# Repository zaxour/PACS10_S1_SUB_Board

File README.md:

# PACS10_S1_SUB_Board

This schematic is, to the best of my ability, a complete capture of the SSUB board found on the PAC-S10 and S1. It is based on the later revision which incorporates the KOSUB board (aka the "bodge board") into the regular layout, as well as the updates made to the audio circuit, which are detailed in a service bulletin. I have included the EAGLE design files (.brd/.sch) as well for anyone that wants to take a crack at laying out the board and producing a new one, if I don't end up doing it at some point.

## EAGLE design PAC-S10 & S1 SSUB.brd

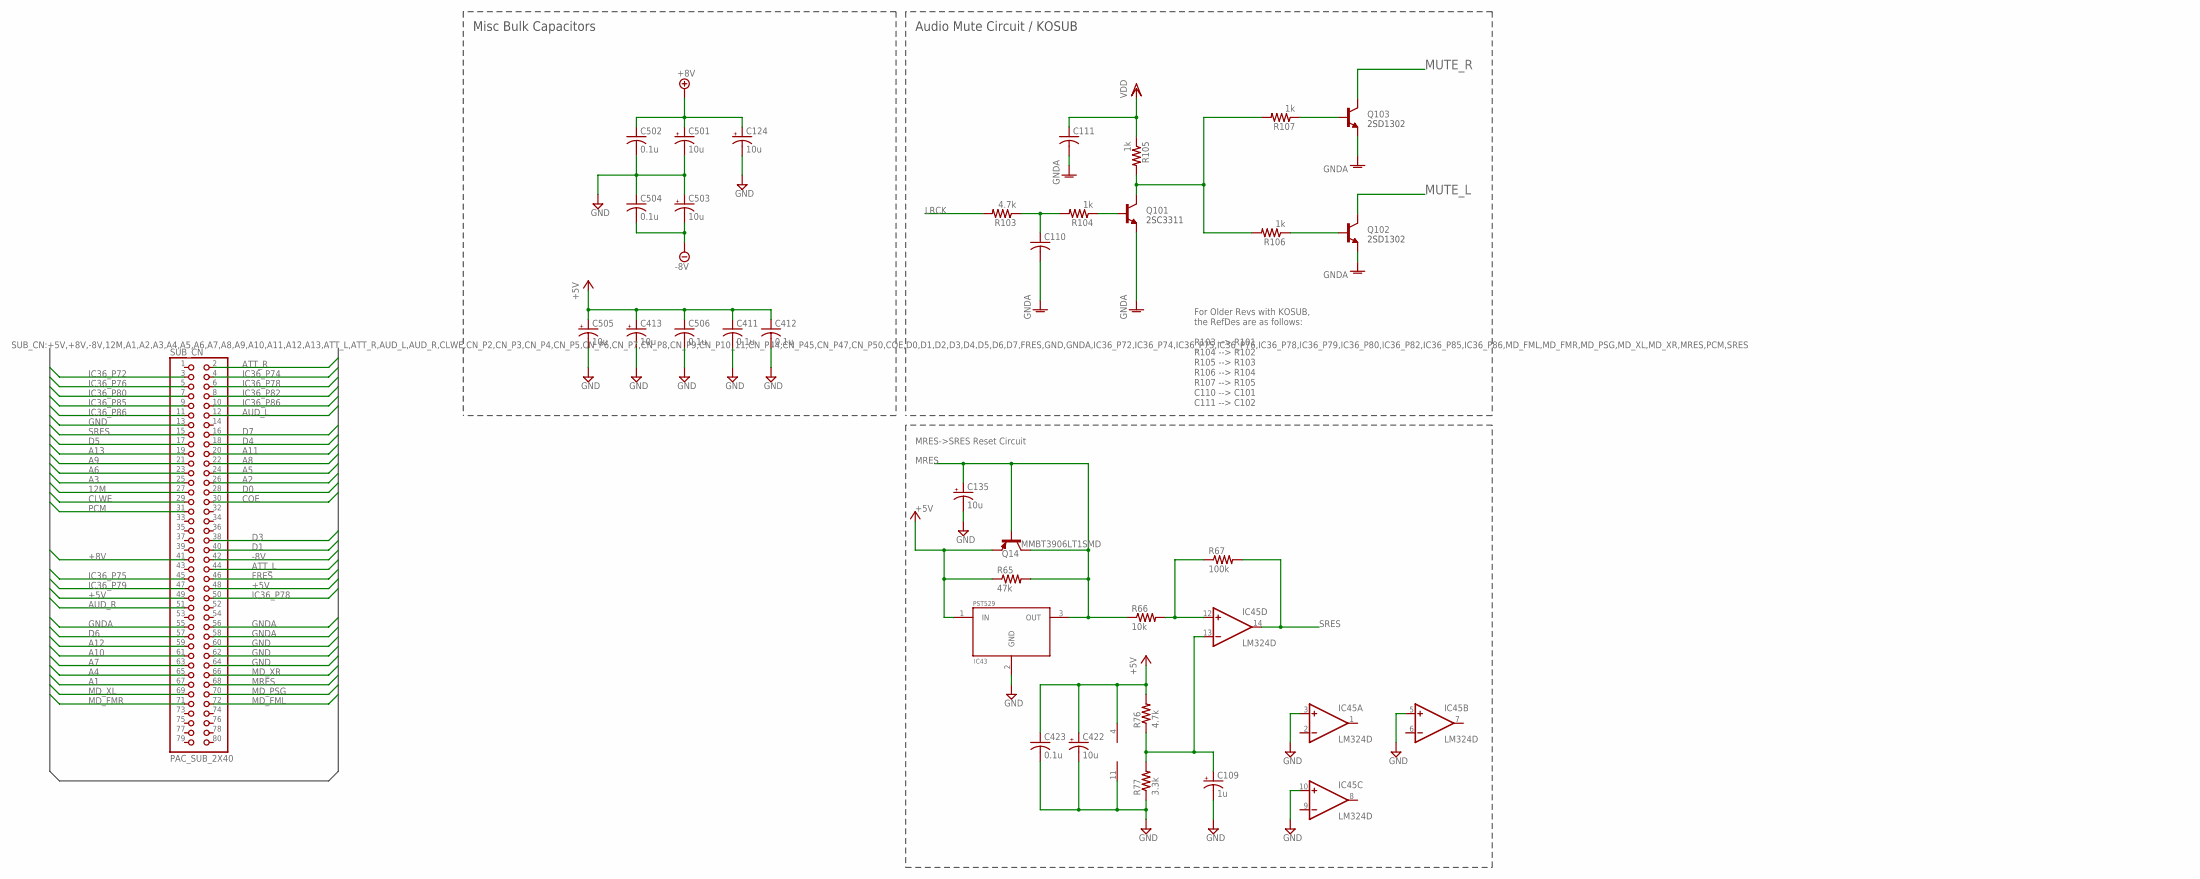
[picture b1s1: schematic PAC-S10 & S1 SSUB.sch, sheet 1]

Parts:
C109: 1u; PANASONIC_B
C110: C-USC1210; C1210
C111: C-USC0805; C0805
C124, C135, C413, C422, C501, C503, C505: 10u; PANASONIC_B
C411, C412, C423, C502, C504, C506: 0.1u; C0805
IC43: PST529; TO92-
IC45: LM324D; SO14
Q14: MMBT3906LT1SMD; SOT23-BEC
Q101, Q102, Q103: MMBT3904LT1-NPN-SOT23-BEC; SOT23-BEC
R65: 47k; R0805
R66: 10k; R0805
R67: 100k; R0805
R76, R103: 4.7k; R0805
R77: 3.3k; R0805
R104, R105, R106, R107: 1k; R0805
SUB_CN: PAC_SUB_2X40; 2X40_STG

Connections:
12M: SUB_CN.27; also elsewhere on the board
+5V: C411.1, C412.1, C413.+, C422.+, C423.1, C505.+, C506.1, IC43.1 (IN), IC45.4 (V+), Q14.E, R65.1, R76.2, SUB_CN.48, SUB_CN.49; also elsewhere on the board
+8V: C124.+, C501.+, C502.1, SUB_CN.41; also elsewhere on the board
-8V: C503.-, C504.2, SUB_CN.42; also elsewhere on the board
A1: SUB_CN.67; also elsewhere on the board
A2: SUB_CN.26; also elsewhere on the board
A3: SUB_CN.25; also elsewhere on the board
A4: SUB_CN.65; also elsewhere on the board
A5: SUB_CN.24; also elsewhere on the board
A6: SUB_CN.23; also elsewhere on the board
A7: SUB_CN.63; also elsewhere on the board
A8: SUB_CN.22; also elsewhere on the board
A9: SUB_CN.21; also elsewhere on the board
A10: SUB_CN.61; also elsewhere on the board
A11: SUB_CN.20; also elsewhere on the board
A12: SUB_CN.59; also elsewhere on the board
A13: SUB_CN.19; also elsewhere on the board
ATT_L: SUB_CN.44; also elsewhere on the board
ATT_R: SUB_CN.2; also elsewhere on the board
AUD_L: SUB_CN.12; also elsewhere on the board
AUD_R: SUB_CN.51; also elsewhere on the board
CLWE: SUB_CN.29; also elsewhere on the board
COE: SUB_CN.30; also elsewhere on the board
D0: SUB_CN.28; also elsewhere on the board
D1: SUB_CN.40; also elsewhere on the board
D3: SUB_CN.38; also elsewhere on the board
D4: SUB_CN.18; also elsewhere on the board
D5: SUB_CN.17; also elsewhere on the board
D6: SUB_CN.57; also elsewhere on the board
D7: SUB_CN.16; also elsewhere on the board
FRES: SUB_CN.46; also elsewhere on the board
GND: C109.-, C124.-, C135.-, C411.2, C412.2, C413.-, C422.-, C423.2, C501.-, C502.2, C503.+, C504.1, C505.-, C506.2, IC43.2 (GND), IC45.3 (+IN), IC45.5 (+IN), IC45.10 (+IN), IC45.11 (V-), R77.1, SUB_CN.13, SUB_CN.60, SUB_CN.62, SUB_CN.64; also elsewhere on the board
GNDA: C110.2, C111.2, Q101.E, Q102.E, Q103.E, SUB_CN.55, SUB_CN.56, SUB_CN.58; also elsewhere on the board
IC36_P72: SUB_CN.3; also elsewhere on the board
IC36_P74: SUB_CN.4; also elsewhere on the board
IC36_P75: SUB_CN.45; also elsewhere on the board
IC36_P76: SUB_CN.5; also elsewhere on the board
IC36_P78: SUB_CN.6, SUB_CN.50; also elsewhere on the board
IC36_P79: SUB_CN.47; also elsewhere on the board
IC36_P80: SUB_CN.7; also elsewhere on the board
IC36_P82: SUB_CN.8; also elsewhere on the board
IC36_P85: SUB_CN.9; also elsewhere on the board
IC36_P86: SUB_CN.10, SUB_CN.11; also elsewhere on the board
LRCK: R103.2; also elsewhere on the board
MD_FML: SUB_CN.72; also elsewhere on the board
MD_FMR: SUB_CN.71; also elsewhere on the board
MD_PSG: SUB_CN.70; also elsewhere on the board
MD_XL: SUB_CN.69; also elsewhere on the board
MD_XR: SUB_CN.66; also elsewhere on the board
MRES: C135.+, IC43.3 (OUT), Q14.B, Q14.C, R65.2, R66.1, SUB_CN.68
MUTE_L: Q102.C; also elsewhere on the board
MUTE_R: Q103.C; also elsewhere on the board
unnamed: IC45.12 (+IN), R66.2, R67.1
unnamed: Q101.B, R104.1
unnamed: C110.1, R103.1, R104.2
unnamed: C109.+, IC45.13 (-IN), R76.1, R77.2
unnamed: Q101.C, R105.2, R106.2, R107.2
unnamed: Q102.B, R106.1
unnamed: Q103.B, R107.1
PCM: SUB_CN.31; also elsewhere on the board
SRES: IC45.14 (OUT), R67.2, SUB_CN.15
VDD: C111.1, R105.1; also elsewhere on the board

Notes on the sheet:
MRES->SRES Reset Circuit
For Older Revs with KOSUB, the RefDes are as follows: R103 --> R101 R104 --> R102 R105 --> R103 R106 --> R104 R107 --> R105 C110 --> C101 C111 --> C102
Audio Mute Circuit / KOSUB
Misc Bulk Capacitors
2SC3311
2SD1302

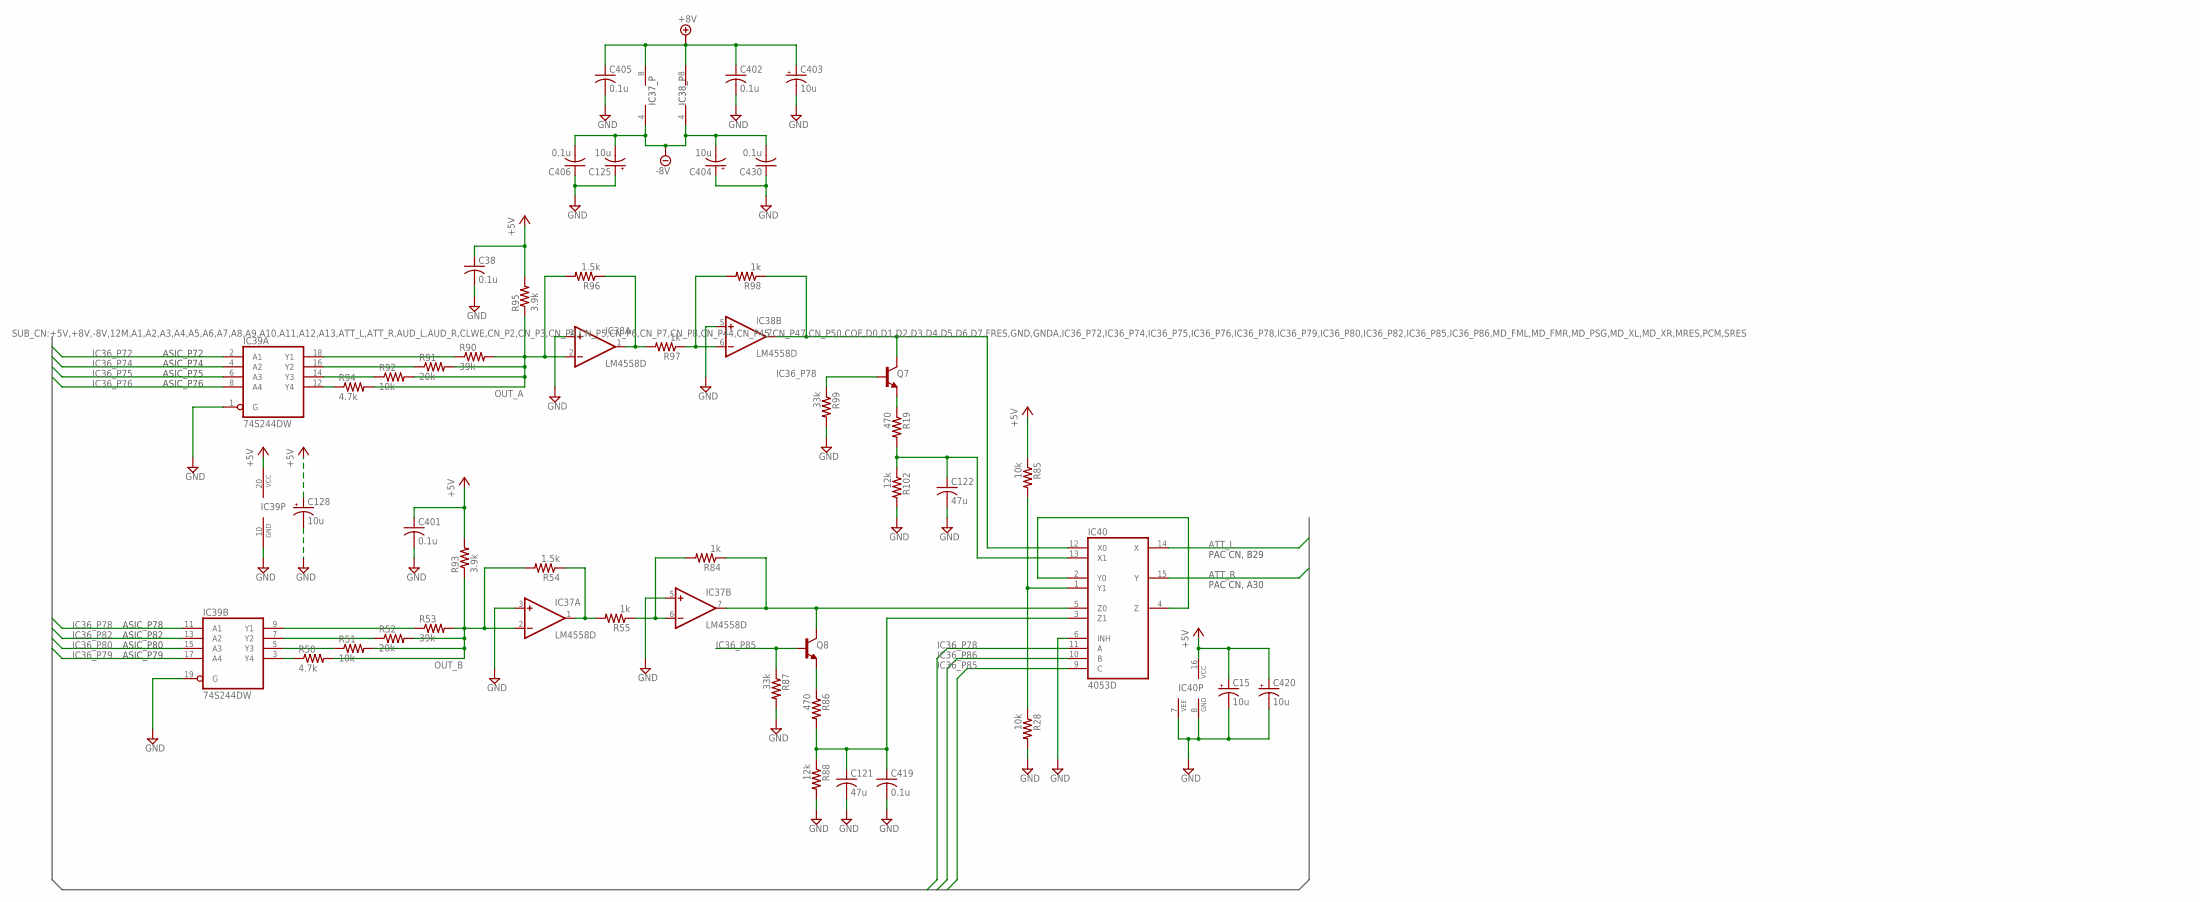
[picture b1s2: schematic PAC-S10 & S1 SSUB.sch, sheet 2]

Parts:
C15, C125, C128, C403, C404, C420: 10u; PANASONIC_B
C38, C401, C402, C405, C406, C419, C430: 0.1u; C0805
C121, C122: 47u; C2220K
IC37, IC38: LM4558D; SO08
IC39: 74S244DW; SO20W
IC40: 4053D; SO16
Q7, Q8: MMBT3904LT1-NPN-SOT23-BEC; SOT23-BEC
R19, R86: 470; R0805
R28, R51, R85, R92: 10k; R0805
R50, R94: 4.7k; R0805
R52, R91: 20k; R0805
R53, R90: 39k; R0805
R54, R96: 1.5k; R0805
R55, R84, R97, R98: 1k; R0805
R87, R99: 33k; R0805
R88, R102: 12k; R0805
R93, R95: 3.9k; R0805

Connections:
+5V: C15.+, C38.1, C128.+, C401.1, C420.+, IC39.20 (VCC), IC40.16 (VCC), R85.1, R93.2, R95.2; also elsewhere on the board
+8V: C402.1, C403.+, C405.1, IC37.8 (V+), IC38.8 (V+); also elsewhere on the board
-8V: C125.-, C404.-, C406.2, C430.2, IC37.4 (V-), IC38.4 (V-); also elsewhere on the board
ATT_L: IC40.14 (X); also elsewhere on the board
ATT_R: IC40.15 (Y); also elsewhere on the board
GND: C15.-, C38.2, C121.2, C122.2, C125.+, C128.-, C401.2, C402.2, C403.-, C404.+, C405.2, C406.1, C419.2, C420.-, C430.1, IC37.3 (+IN), IC37.5 (+IN), IC38.3 (+IN), IC38.5 (+IN), IC39.1 (G), IC39.10 (GND), IC39.19 (G), IC40.6 (INH), IC40.7 (VEE), IC40.8 (GND), R28.2, R87.2, R88.2, R99.2, R102.2; also elsewhere on the board
IC36_P72: IC39.2 (A1); also elsewhere on the board
IC36_P74: IC39.4 (A2); also elsewhere on the board
IC36_P75: IC39.6 (A3); also elsewhere on the board
IC36_P76: IC39.8 (A4); also elsewhere on the board
IC36_P78: IC39.11 (A1), IC40.11 (A), Q7.B, R99.1; also elsewhere on the board
IC36_P79: IC39.17 (A4); also elsewhere on the board
IC36_P80: IC39.15 (A3); also elsewhere on the board
IC36_P82: IC39.13 (A2); also elsewhere on the board
IC36_P85: IC40.9 (C), Q8.B, R87.1; also elsewhere on the board
IC36_P86: IC40.10 (B); also elsewhere on the board
IC40_P3: C121.1, C419.1, IC40.3 (Z1), R86.2, R88.1
unnamed: IC39.3 (Y4), R50.1
unnamed: IC39.5 (Y3), R51.1
unnamed: IC39.7 (Y2), R52.1
unnamed: IC39.9 (Y1), R53.1
unnamed: IC37.1 (OUT), R54.1, R55.2
unnamed: IC39.12 (Y4), R94.1
unnamed: IC39.14 (Y3), R92.1
unnamed: IC39.16 (Y2), R91.1
unnamed: IC39.18 (Y1), R90.1
unnamed: IC40.2 (Y0), IC40.4 (Z)
unnamed: IC37.6 (-IN), R55.1, R84.2
unnamed: Q8.E, R86.1
unnamed: IC40.1 (Y1), R28.1, R85.2
unnamed: IC38.6 (-IN), R97.1, R98.2
unnamed: IC38.1 (OUT), R96.1, R97.2
unnamed: IC37.7 (OUT), IC40.5 (Z0), Q8.C, R84.1
unnamed: IC38.7 (OUT), IC40.12 (X0), Q7.C, R98.1
unnamed: Q7.E, R19.1
unnamed: C122.1, IC40.13 (X1), R19.2, R102.1
OUT_A: IC38.2 (-IN), R90.2, R91.2, R92.2, R94.2, R95.1, R96.2
OUT_B: IC37.2 (-IN), R50.2, R51.2, R52.2, R53.2, R54.2, R93.1

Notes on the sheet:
IC37_P
IC38_P
ASIC_P72
ASIC_P74
ASIC_P75
ASIC_P76
ASIC_P78
ASIC_P82
ASIC_P80
ASIC_P79
PAC CN, A30
PAC CN, B29

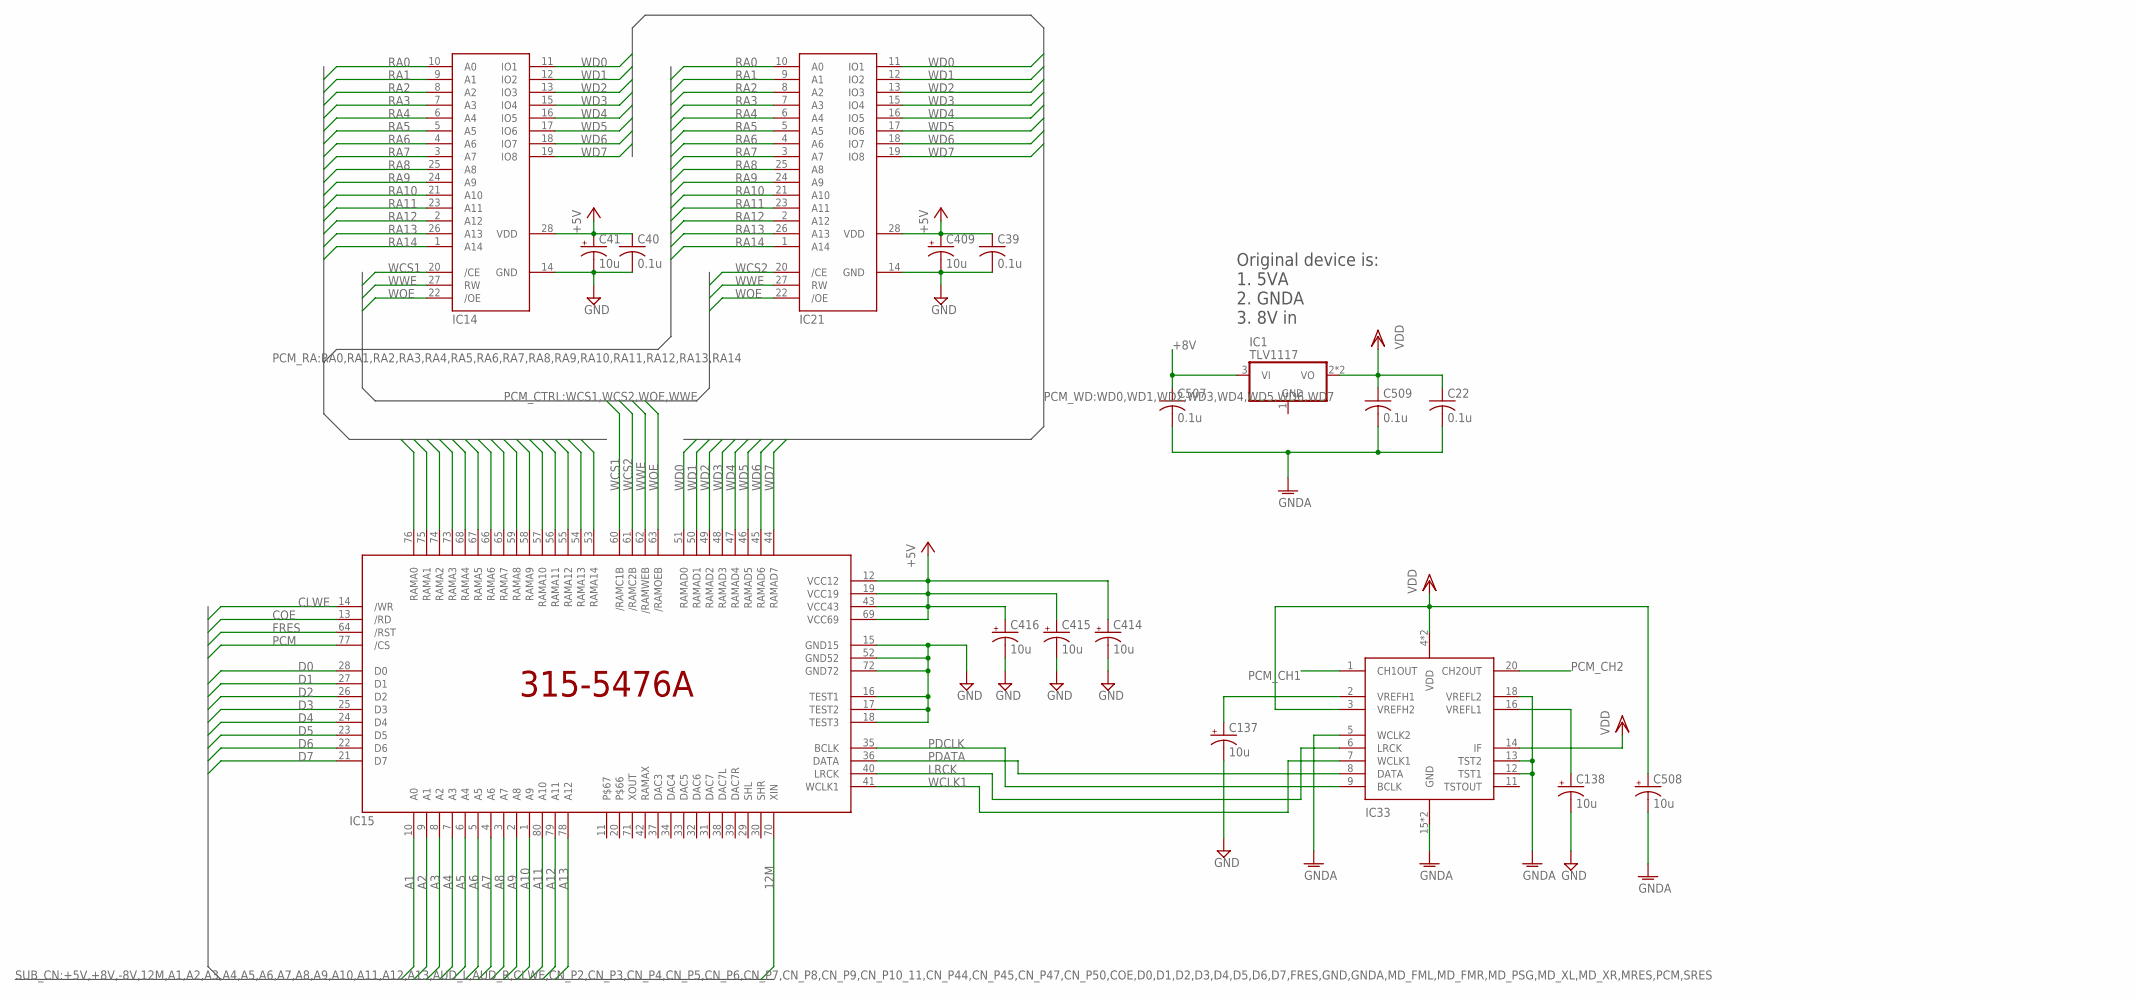
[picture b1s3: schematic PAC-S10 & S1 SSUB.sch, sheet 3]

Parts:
C22, C39, C40, C507, C509: 0.1u; C0805
C41, C137, C138, C409, C414, C415, C416, C508: 10u; PANASONIC_B
IC1: TLV1117; SOT223
IC14, IC21: TC51832F-10; SOP28
IC15: 315-5476A; QFP80R
IC33: LC7881M; SOIC20S

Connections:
12M: IC15.70 (XIN); also elsewhere on the board
+5V: C39.1, C40.1, C41.+, C409.+, C414.+, C415.+, C416.+, IC14.28 (VDD), IC15.12 (VCC12), IC15.19 (VCC19), IC15.43 (VCC43), IC15.69 (VCC69), IC21.28 (VDD); also elsewhere on the board
+8V: C507.1, IC1.3 (VI); also elsewhere on the board
A1: IC15.10 (A0); also elsewhere on the board
A2: IC15.9 (A1); also elsewhere on the board
A3: IC15.8 (A2); also elsewhere on the board
A4: IC15.7 (A3); also elsewhere on the board
A5: IC15.6 (A4); also elsewhere on the board
A6: IC15.5 (A5); also elsewhere on the board
A7: IC15.4 (A6); also elsewhere on the board
A8: IC15.3 (A7); also elsewhere on the board
A9: IC15.2 (A8); also elsewhere on the board
A10: IC15.1 (A9); also elsewhere on the board
A11: IC15.80 (A10); also elsewhere on the board
A12: IC15.79 (A11); also elsewhere on the board
A13: IC15.78 (A12); also elsewhere on the board
CLWE: IC15.14 (/WR); also elsewhere on the board
COE: IC15.13 (/RD); also elsewhere on the board
D0: IC15.28 (D0); also elsewhere on the board
D1: IC15.27 (D1); also elsewhere on the board
D2: IC15.26 (D2)
D3: IC15.25 (D3); also elsewhere on the board
D4: IC15.24 (D4); also elsewhere on the board
D5: IC15.23 (D5); also elsewhere on the board
D6: IC15.22 (D6); also elsewhere on the board
D7: IC15.21 (D7); also elsewhere on the board
FRES: IC15.64 (/RST); also elsewhere on the board
GND: C39.2, C40.2, C41.-, C137.-, C138.-, C409.-, C414.-, C415.-, C416.-, IC14.14 (GND), IC15.15 (GND15), IC15.16 (TEST1), IC15.17 (TEST2), IC15.18 (TEST3), IC15.52 (GND52), IC15.72 (GND72), IC21.14 (GND), IC33.15 (GND), IC33.17 (GND); also elsewhere on the board
GNDA: C22.2, C507.2, C508.-, C509.2, IC33.5 (WCLK2), IC33.12 (TST1), IC33.13 (TST2), IC33.18 (VREFL2); also elsewhere on the board
LRCK: IC15.40 (LRCK), IC33.6 (LRCK); also elsewhere on the board
unnamed: C138.+, IC33.16 (VREFL1)
unnamed: C137.+, IC33.2 (VREFH1)
PCM: IC15.77 (/CS); also elsewhere on the board
PCM_CH1: IC33.1 (CH1OUT); also elsewhere on the board
PCM_CH2: IC33.20 (CH2OUT); also elsewhere on the board
PDATA: IC15.36 (DATA), IC33.8 (DATA)
PDCLK: IC15.35 (BCLK), IC33.9 (BCLK)
RA0: IC14.10 (A0), IC15.76 (RAMA0), IC21.10 (A0)
RA1: IC14.9 (A1), IC15.75 (RAMA1), IC21.9 (A1)
RA2: IC14.8 (A2), IC15.74 (RAMA2), IC21.8 (A2)
RA3: IC14.7 (A3), IC15.73 (RAMA3), IC21.7 (A3)
RA4: IC14.6 (A4), IC15.68 (RAMA4), IC21.6 (A4)
RA5: IC14.5 (A5), IC15.67 (RAMA5), IC21.5 (A5)
RA6: IC14.4 (A6), IC15.66 (RAMA6), IC21.4 (A6)
RA7: IC14.3 (A7), IC15.65 (RAMA7), IC21.3 (A7)
RA8: IC14.25 (A8), IC15.59 (RAMA8), IC21.25 (A8)
RA9: IC14.24 (A9), IC15.58 (RAMA9), IC21.24 (A9)
RA10: IC14.21 (A10), IC15.57 (RAMA10), IC21.21 (A10)
RA11: IC14.23 (A11), IC15.56 (RAMA11), IC21.23 (A11)
RA12: IC14.2 (A12), IC15.55 (RAMA12), IC21.2 (A12)
RA13: IC14.26 (A13), IC15.54 (RAMA13), IC21.26 (A13)
RA14: IC14.1 (A14), IC15.53 (RAMA14), IC21.1 (A14)
VDD: C22.1, C508.+, C509.1, IC1.2 (VO), IC1.4 (VO), IC33.3 (VREFH2), IC33.4 (VDD), IC33.10 (VDD), IC33.14 (IF); also elsewhere on the board
WCLK1: IC15.41 (WCLK1), IC33.7 (WCLK1)
WCS1: IC14.20 (/CE), IC15.60 (/RAMC1B)
WCS2: IC15.61 (/RAMC2B), IC21.20 (/CE)
WD0: IC14.11 (IO1), IC15.51 (RAMAD0), IC21.11 (IO1)
WD1: IC14.12 (IO2), IC15.50 (RAMAD1), IC21.12 (IO2)
WD2: IC14.13 (IO3), IC15.49 (RAMAD2), IC21.13 (IO3)
WD3: IC14.15 (IO4), IC15.48 (RAMAD3), IC21.15 (IO4)
WD4: IC14.16 (IO5), IC15.47 (RAMAD4), IC21.16 (IO5)
WD5: IC14.17 (IO6), IC15.46 (RAMAD5), IC21.17 (IO6)
WD6: IC14.18 (IO7), IC15.45 (RAMAD6), IC21.18 (IO7)
WD7: IC14.19 (IO8), IC15.44 (RAMAD7), IC21.19 (IO8)
WOE: IC14.22 (/OE), IC15.63 (/RAMOEB), IC21.22 (/OE)
WWE: IC14.27 (RW), IC15.62 (/RAMWEB), IC21.27 (RW)

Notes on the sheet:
Original device is: 1. 5VA 2. GNDA 3. 8V in

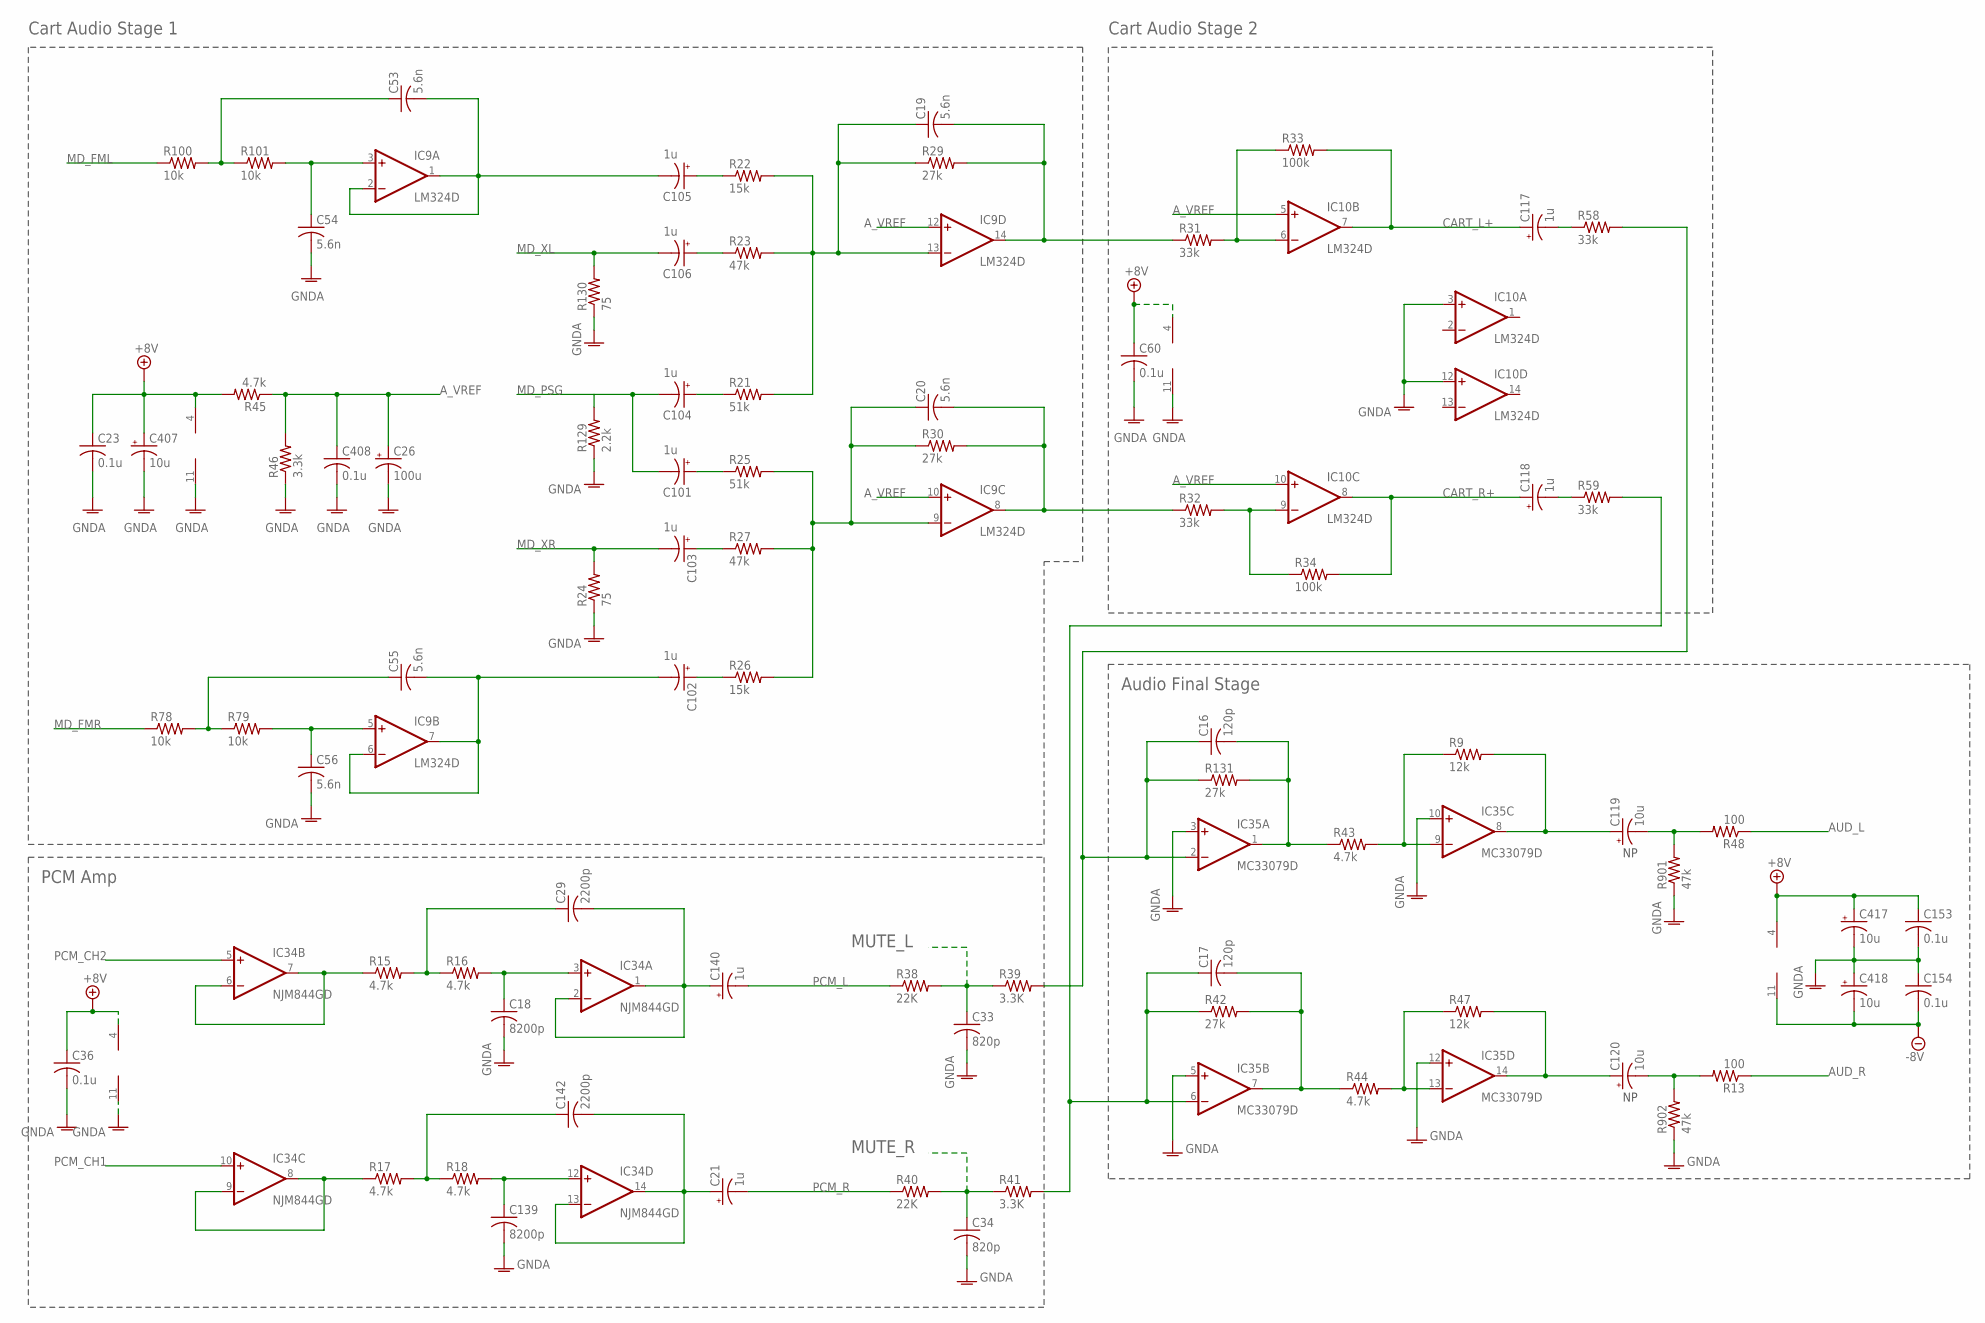
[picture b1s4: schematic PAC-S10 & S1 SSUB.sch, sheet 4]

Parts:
C16, C17: 120p; C0805
C18, C139: 8200p; C0805
C19, C20, C53, C54, C55, C56: 5.6n; C0805
C21, C117, C118, C140: 1u; PANASONIC_D
C23, C36, C60, C153, C154, C408: 0.1u; C0805
C26: 100u; PANASONIC_E
C29, C142: 2200p; C0805
C33, C34: 820p; C0805
C101, C102, C103, C104, C105, C106: 1u; PANASONIC_C
C119, C120: 10u; PANASONIC_D
C407, C417, C418: 10u; PANASONIC_B
IC9, IC10: LM324D; SO14
IC34: NJM844GD; SO14
IC35: MC33079D; SO14
R9, R47: 12k; R0805
R13, R48: 100; R0805
R15, R16, R17, R18, R43, R44, R45: 4.7k; R0805
R21, R25: 51k; R0805
R22, R26: 15k; R0805
R23, R27, R901, R902: 47k; R0805
R24, R130: 75; R0805
R29, R30, R42, R131: 27k; R0805
R31, R32, R58, R59: 33k; R0805
R33, R34: 100k; R0805
R38, R40: 22K; R0805
R39, R41: 3.3K; R0805
R46: 3.3k; R0805
R78, R79, R100, R101: 10k; R0805
R129: 2.2k; R0805

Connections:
+8V: C23.1, C36.1, C60.1, C153.1, C407.+, C417.+, IC9.4 (V+), IC10.4 (V+), IC34.4 (V+), IC35.4 (V+), R45.2; also elsewhere on the board
-8V: C154.2, C418.-, IC35.11 (V-); also elsewhere on the board
AUD_L: R48.1; also elsewhere on the board
AUD_R: R13.1; also elsewhere on the board
A_VREF: C26.+, C408.1, IC9.10 (+IN), IC9.12 (+IN), IC10.5 (+IN), IC10.10 (+IN), R45.1, R46.2
CART_L: C117.-, R58.1
CART_L+: C117.+, IC10.7 (OUT), R33.2
CART_R: C118.-, R59.1
CART_R+: C118.+, IC10.8 (OUT), R34.2
GNDA: C18.2, C23.2, C26.-, C33.2, C34.2, C36.2, C54.2, C56.2, C60.2, C139.2, C153.2, C154.1, C407.-, C408.2, C417.-, C418.+, IC9.11 (V-), IC10.3 (+IN), IC10.11 (V-), IC10.12 (+IN), IC34.11 (V-), IC35.3 (+IN), IC35.5 (+IN), IC35.10 (+IN), IC35.12 (+IN), R24.1, R46.1, R129.1, R130.1, R901.1, R902.1; also elsewhere on the board
MD_FML: R100.1; also elsewhere on the board
MD_FMR: R78.1; also elsewhere on the board
MD_PSG: C101.-, C104.-, R129.2; also elsewhere on the board
MD_XL: C106.-, R130.2; also elsewhere on the board
MD_XR: C103.-, R24.2; also elsewhere on the board
MUTE_L: C33.1, R38.2, R39.1; also elsewhere on the board
MUTE_R: C34.1, R40.2, R41.1; also elsewhere on the board
unnamed: C54.1, IC9.3 (+IN), R101.2
unnamed: C53.1, R100.2, R101.1
unnamed: C56.1, IC9.5 (+IN), R79.2
unnamed: C53.2, C105.-, IC9.1 (OUT), IC9.2 (-IN)
unnamed: C55.2, C102.-, IC9.6 (-IN), IC9.7 (OUT)
unnamed: C55.1, R78.2, R79.1
unnamed: C106.+, R23.1
unnamed: C19.1, IC9.13 (-IN), R21.2, R22.2, R23.2, R29.1
unnamed: C104.+, R21.1
unnamed: C101.+, R25.1
unnamed: C105.+, R22.1
unnamed: C20.1, IC9.9 (-IN), R25.2, R26.2, R27.2, R30.1
unnamed: C103.+, R27.1
unnamed: C102.+, R26.1
unnamed: IC10.9 (-IN), R32.2, R34.1
unnamed: C19.2, IC9.14 (OUT), R29.2, R31.1
unnamed: IC10.6 (-IN), R31.2, R33.1
unnamed: C20.2, IC9.8 (OUT), R30.2, R32.1
unnamed: IC34.8 (OUT), IC34.9 (-IN), R17.1
unnamed: IC34.6 (-IN), IC34.7 (OUT), R15.1
unnamed: C142.1, R17.2, R18.1
unnamed: C18.1, IC34.3 (+IN), R16.2
unnamed: C29.2, C140.+, IC34.1 (OUT), IC34.2 (-IN)
unnamed: C29.1, R15.2, R16.1
unnamed: C139.1, IC34.12 (+IN), R18.2
unnamed: C21.+, C142.2, IC34.13 (-IN), IC34.14 (OUT)
unnamed: IC35.13 (-IN), R44.2, R47.1
unnamed: C16.2, IC35.1 (OUT), R43.1, R131.2
unnamed: IC35.9 (-IN), R9.1, R43.2
unnamed: C17.2, IC35.7 (OUT), R42.2, R44.1
unnamed: C120.-, R13.2, R902.2
unnamed: C119.-, R48.2, R901.2
unnamed: C120.+, IC35.14 (OUT), R47.2
unnamed: C119.+, IC35.8 (OUT), R9.2
unnamed: C17.1, IC35.6 (-IN), R41.2, R42.1, R59.2
unnamed: C16.1, IC35.2 (-IN), R39.2, R58.2, R131.1
PCM_CH1: IC34.10 (+IN); also elsewhere on the board
PCM_CH2: IC34.5 (+IN); also elsewhere on the board
PCM_L: C140.-, R38.1
PCM_R: C21.-, R40.1

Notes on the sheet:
Cart Audio Stage 1
Cart Audio Stage 2
Audio Final Stage
PCM Amp

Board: 2 copper layers, 177 parts (47 on the bottom side), 161 nets, no tracks yet.

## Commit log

2022-07-15 Add files via upload
    Q14 is diode connected, uploading corrected files
2022-08-19 Add files via upload
    Corrected resistor reference designators (R32, R34)
